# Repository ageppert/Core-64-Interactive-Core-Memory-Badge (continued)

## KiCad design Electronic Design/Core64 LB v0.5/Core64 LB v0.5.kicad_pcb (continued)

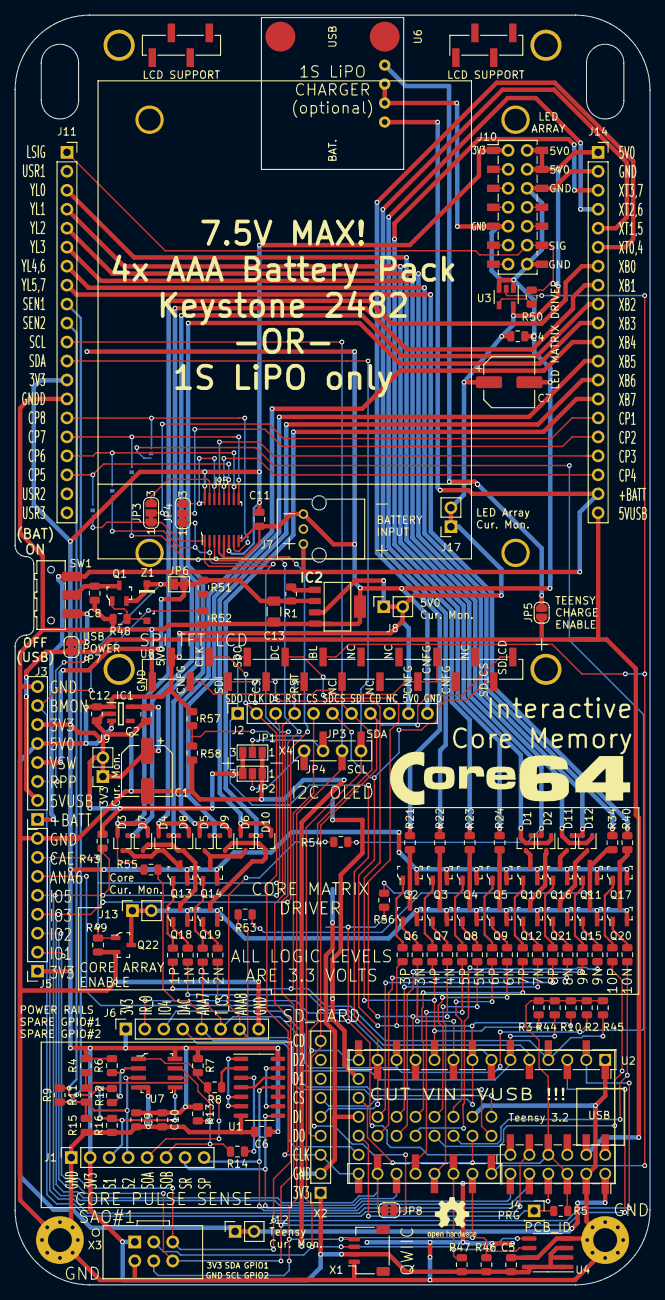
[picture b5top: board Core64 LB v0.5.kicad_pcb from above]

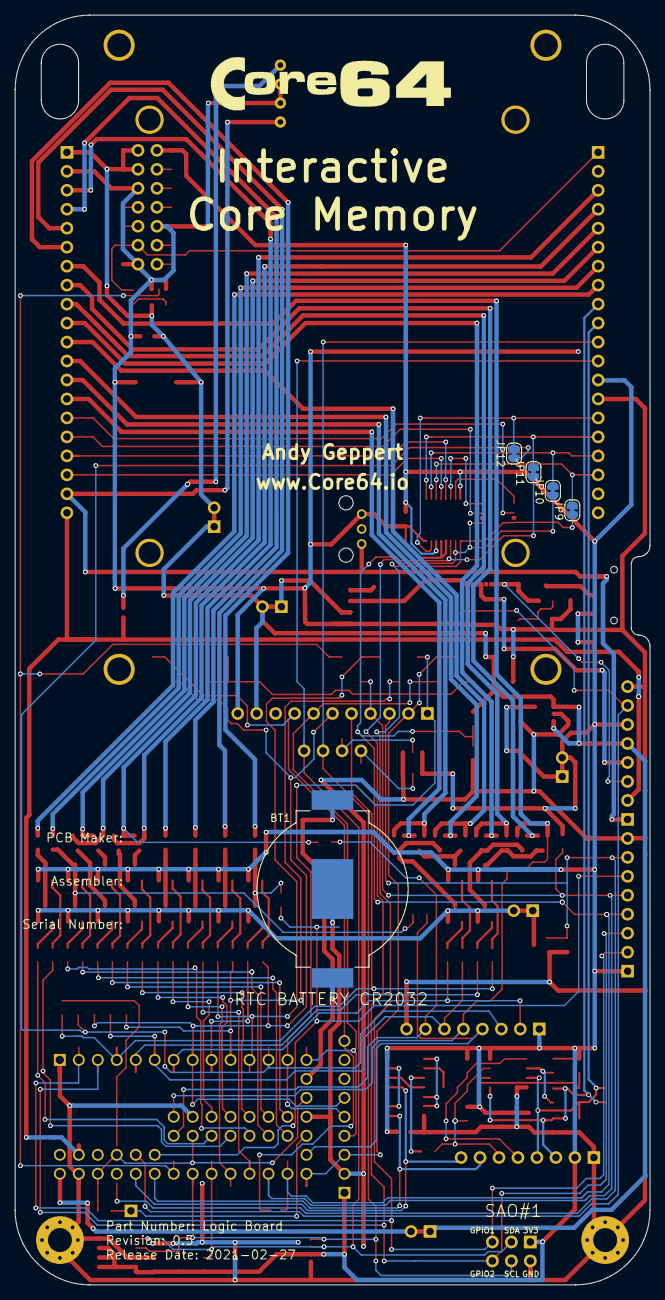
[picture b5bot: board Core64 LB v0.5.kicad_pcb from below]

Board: 2 copper layers, 85.0 x 170.0 mm, 153 parts (6 on the bottom side), 134 nets.

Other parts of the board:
JP8: SD CARD DETECT; SolderJumper-2_P1.3mm_Open_RoundedPad1.0x1.5mm

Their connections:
5V0_MON: JP8.1; also elsewhere on the board
SD_SPI_CD: JP8.2; also elsewhere on the board

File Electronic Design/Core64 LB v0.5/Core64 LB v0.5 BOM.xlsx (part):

Source: | /Users/ageppert/Dropbox/Electronics/Core 64 Interactive Badge/Core-64-Interacti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
Date: | Friday, March 12, 2021 at 07:06:22 PM
Tool: | Eeschema (5.1.2-1)-1
Generator: | /private/var/folders/kh/1q_kd4hn7cq821df7xpmdhbw0000gn/T/AppTranslocation/51E6E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
Component Count: | 153
Ref | Qnty | Value | Cmp name | Footprint | Description | Vendor
BT1, | 1 | 3V | Battery_Cell | Battery:BatteryHolder_MPD_BC2003_1x2032 | Single-cell battery
C2, C12, | 2 | 1uF | C | Capacitor_SMD:C_0805_2012Metric | Unpolarized capacitor
C7, C1, | 2 | 470uF | CP1_Small | Capacitor_SMD:CP_Elec_6.3x7.7 | Polarized capacitor, small US symbol
C8, | 1 | 0.01uF | C | Capacitor_SMD:C_0805_2012Metric | Unpolarized capacitor
C9, C6, C4, C5, C11, | 5 | 0.1uF | C | Capacitor_SMD:C_0805_2012Metric | Unpolarized capacitor
C10, | 1 | 10uF | C | Capacitor_SMD:C_0805_2012Metric | Unpolarized capacitor
C13, | 1 | 68uF | C | Capacitor_SMD:C_1206_3216Metric | Unpolarized capacitor
D3, D4, D5, D6, D11, D1, | 6 | BAT54AW | BAT54AW | Package_TO_SOT_SMD:SOT-323_SC-70 | Dual schottky barrier diode, common anode, SOT-323
D7, D8, D10, D9, D12, D2, | 6 | BAT54CW | BAT54CW | Package_TO_SOT_SMD:SOT-323_SC-70 | Dual schottky barrier diode, common cathode, SOT-323
H2, H1, | 2 | GND PAD | MountingHole_Pad | MountingHole:MountingHole_3.2mm_M3_Pad_Via | Mounting Hole with connection
IC1, | 1 | TPS7A0533PDBVR | TPS7A0533PDBVR | TPS7A0533PDBVR:SOT95P280X145-5N | 1-A, ultra-low-IQ, 200-mA low-dropout (LDO) regulator in a small-sized package
IC2, | 1 | LP3961EMP-5.0 | LP3961EMP-5.0 | LP3961EMP-5.0:SOT150P696X180-5N | Fast Ultra Low Dropout Linear Regulators
J1, J5, J6, | 3 | HEADER_8-PIN_0.1 | Conn_01x08 | Connector_PinSocket_2.54mm:PinSocket_1x08_P2.54mm_Vertical | Generic connector, single row, 01x08, script generated (kicad-library-utils/sch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
J2, | 1 | HEADER_11-PIN_0.1 | Conn_01x11 | Connector_PinSocket_2.54mm:PinSocket_1x11_P2.54mm_Vertical | Generic connector, single row, 01x11, script generated (kicad-library-utils/sch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
J3, | 1 | Conn_01x08_Female | Conn_01x08_Female | Connector_PinSocket_2.54mm:PinSocket_1x08_P2.54mm_Vertical | Generic connector, single row, 01x08, script generated (kicad-library-utils/sch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
J4, | 1 | PRG | Conn_01x01 | Connector_PinSocket_2.54mm:PinSocket_1x01_P2.54mm_Vertical | Generic connector, single row, 01x01, script generated (kicad-library-utils/sch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
J7, | 1 | S03B-PASK-2_LF__SN_ | S03B-PASK-2_LF__SN_ | JST_S03B-PASK-2_LF__SN_:S03BPASK2LFSN_.075in_holes | JST (JAPAN SOLDERLESS TERMINALS) - S03B-PASK-2(LF)(SN) - HEADER, PA, 3WAY, SIDE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
J8, | 1 | 5V0 Cur. Mon. | Conn_01x02 | Connector_PinSocket_2.54mm:PinSocket_1x02_P2.54mm_Vertical | Generic connector, single row, 01x02, script generated (kicad-library-utils/sch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
J9, | 1 | 3V3 Cur. Mon. | Conn_01x02 | Connector_PinSocket_2.54mm:PinSocket_1x02_P2.54mm_Vertical | Generic connector, single row, 01x02, script generated (kicad-library-utils/sch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
J10, | 1 | TSM-106-03-T-DV‚Äé | Conn_02x07_Odd_Even | Connector_PinHeader_2.54mm:PinHeader_2x07_P2.54mm_Vertical_SMD_and_TH | Generic connector, double row, 02x07, odd/even pin numbering scheme (row 1 odd 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
J12, | 1 | TEENSY Cur. Mon. | Conn_01x02 | Connector_PinSocket_2.54mm:PinSocket_1x02_P2.54mm_Vertical | Generic connector, single row, 01x02, script generated (kicad-library-utils/sch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
J13, | 1 | Core Cur. Mon. | Conn_01x02 | Connector_PinSocket_2.54mm:PinSocket_1x02_P2.54mm_Vertical | Generic connector, single row, 01x02, script generated (kicad-library-utils/sch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
J14, J11, | 2 | SSW-116-22-F-S-VS‚Äé | Conn_01x20 | Connector_PinSocket_2.54mm:PinSocket_1x20_P2.54mm_Vertical | Generic connector, single row, 01x20, script generated (kicad-library-utils/sch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
J17, | 1 | LED Cur. Mon. | Conn_01x02 | Connector_PinSocket_2.54mm:PinSocket_1x02_P2.54mm_Vertical | Generic connector, single row, 01x02, script generated (kicad-library-utils/sch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
JP2, JP1, | 2 | SolderJumper_3_Open | SolderJumper_3_Open | Jumper:SolderJumper-3_P1.3mm_Open_Pad1.0x1.5mm_NumberLabels | Solder Jumper, 3-pole, open
JP4, JP3, | 2 | SolderJumper_3_Open | SolderJumper_3_Bridged12 | Jumper:SolderJumper-3_P1.3mm_Bridged12_RoundedPad1.0x1.5mm_NumberLabels | 3-pole Solder Jumper, pins 1+2 closed/bridged
JP5, | 1 | Teensy_Charge_Enable | SolderJumper_2_Open | Jumper:SolderJumper-2_P1.3mm_Open_RoundedPad1.0x1.5mm | Solder Jumper, 2-pole, open
JP6, | 1 | Opt. Cur. Mon. | SolderJumper_2_Bridged | Jumper:SolderJumper-2_P1.3mm_Bridged_Pad1.0x1.5mm | Solder Jumper, 2-pole, closed/bridged
JP7, | 1 | USB_Power_Enable | SolderJumper_2_Bridged | Jumper:SolderJumper-2_P1.3mm_Bridged_RoundedPad1.0x1.5mm | Solder Jumper, 2-pole, closed/bridged
JP8, | 1 | SD CARD DETECT | SolderJumper_2_Open | Jumper:SolderJumper-2_P1.3mm_Open_RoundedPad1.0x1.5mm | Solder Jumper, 2-pole, open
JP9, | 1 | Hall Switch 1 | SolderJumper_2_Bridged | Jumper:SolderJumper-2_P1.3mm_Bridged_RoundedPad1.0x1.5mm | Solder Jumper, 2-pole, closed/bridged
JP10, | 1 | Hall Switch 2 | SolderJumper_2_Bridged | Jumper:SolderJumper-2_P1.3mm_Bridged_RoundedPad1.0x1.5mm | Solder Jumper, 2-pole, closed/bridged
JP11, | 1 | Hall Switch 3 | SolderJumper_2_Bridged | Jumper:SolderJumper-2_P1.3mm_Bridged_RoundedPad1.0x1.5mm | Solder Jumper, 2-pole, closed/bridged
JP12, | 1 | Hall Switch 4 | SolderJumper_2_Bridged | Jumper:SolderJumper-2_P1.3mm_Bridged_RoundedPad1.0x1.5mm | Solder Jumper, 2-pole, closed/bridged
L1, L2, | 2 | Core_64_Logo | Core_64_Logo | Core_Memory_8x8_Array:Core64_Logo
L4, | 1 | Logo_Open_Hardware_Small | Logo_Open_Hardware_Small | Symbol:OSHW-Logo2_7.3x6mm_SilkScreen | Open Hardware logo, small
Q1, | 1 | MCC_SL3401A | Q_PMOS_GSD | Digikey:SOT-23-3 | P-MOSFET transistor, gate/source/drain
Q2, Q14, Q4, Q5, Q10, Q16, Q11, Q17, Q13, Q3, | 10 | MMBT4403LT1G | MMBT4403LT1G | Digikey:SOT-23-3 | TRANS PNP 40V 0.6A SOT23
Q6, Q19, Q8, Q9, Q12, Q21, Q15, Q20, Q18, Q7, | 10 | MMBT4401LT1G | MMBT4401LT1G | Digikey:SOT-23-3 | TRANS NPN 40V 0.6A SOT23
Q22, | 1 | Q_NMOS_DGS_NVTR4503NT1G | Q_NMOS_GSD | Digikey:SOT-23-3 | N-MOSFET transistor, gate/source/drain
R4, R6, | 2 | 1K8-1% | R | Resistor_SMD:R_0805_2012Metric | Resistor
R5, R43, R53, R55, R54, R56, R7, R13, R14, R8, R3, R10, R44, R45, R2, R1, R48, 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 | 18 | 10k | R | Resistor_SMD:R_0805_2012Metric | Resistor
R11, R12, | 2 | 11-1% | R | Resistor_SMD:R_0805_2012Metric | Resistor
R15, R9, R16, | 3 | 1K5-1% | R | Resistor_SMD:R_0805_2012Metric | Resistor
R21, R22, R24, R23, R34, R40, | 6 | 6R8-1% | R | Resistor_SMD:R_0805_2012Metric | Resistor
R46, R47, | 2 | 2K2 | R | Resistor_SMD:R_0805_2012Metric | Resistor
R50, R17, R25, R33, R39, R18, R26, R19, R27, R20, R28, R29, R31, R36, R42, R30,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 | 21 | 470 | R | Resistor_SMD:R_0805_2012Metric | Resistor
R51, | 1 | 33k | R | Resistor_SMD:R_0805_2012Metric | Resistor
R52, R57, R58, | 3 | 11k | R | Resistor_SMD:R_0805_2012Metric | Resistor
SW1, | 1 | JS102011SAQN | SW_SPDT | Button_Switch_SMD:SW_SPDT_CK-JS102011SAQN_Core64_Recessed | Switch, single pole double throw
U1, | 1 | 74HC02 | 74HC02 | Package_SO:SOIC-14_3.9x8.7mm_P1.27mm | quad 2-input NOR gate
U2, | 1 | Teensy3.2 | Teensy3.2 | Teensy:Teensy30_31_32_LC_SMD_SOCKETS
U3, | 1 | SN74LV1T125DBVR | SN74LV1T125DBVR | Package_TO_SOT_SMD:SOT-23-5 | Single Power Supply Single Buffer Gate with 3-State Output CMOS Logic Level Shi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
U4, | 1 | M24C01-RMN | M24C01-RMN | Package_SO:SOIC-8_3.9x4.9mm_P1.27mm | 1Kb (128x8) I2C Serial EEPROM, 1.8-5.5V, SOIC-8
U5, | 1 | 74HC238 | 74HC238 | Digikey:TSSOP-16-W4.40mm
U6, | 1 | Micro_LiPo_Charger | Micro_LiPo_Charger | Core_Memory_8x8_Array:Micro_LiPo_Charger_CornerSMD
U7, | 1 | LM393 | LM393 | Digikey:SOIC-8_W3.9mm | Low-Power, Low-Offset Voltage, Dual Comparators, DIP-8/SOIC-8/SSOP-8
U8, | 1 | Adafruit_3.2_TFT_1743 | Adafruit_3.2_TFT_1743 | Adafruit_3.2_TFT:Adafruit_3.2_TFT_Dual_PinHeader_1x20_P2.54mm_Vertical_SMD_Pin1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 | Adafruit 3.2 TFT Breakout Board with resistive touch screen
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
